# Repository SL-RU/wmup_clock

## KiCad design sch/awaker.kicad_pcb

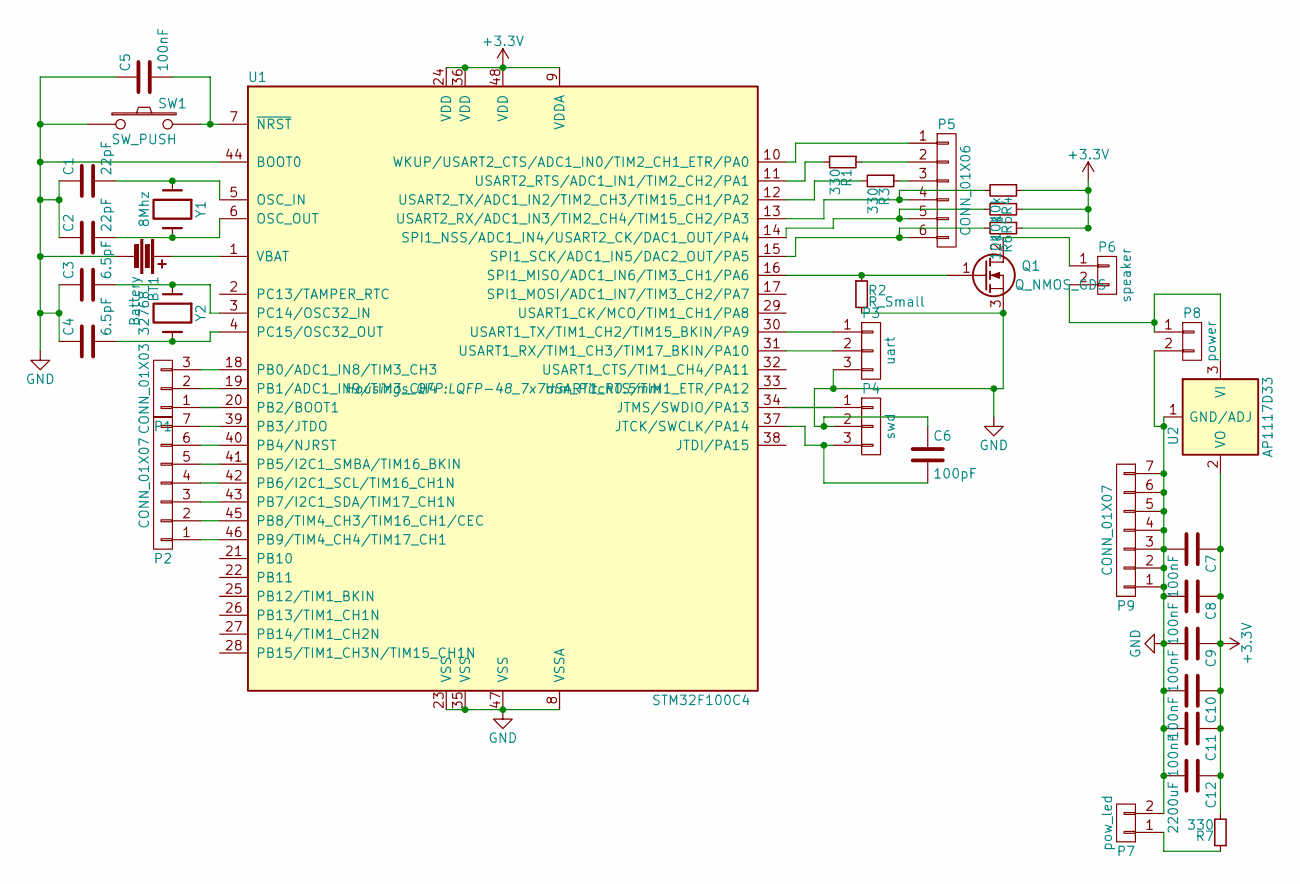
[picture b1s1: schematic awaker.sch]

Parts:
BT1: Battery; BS-7_CR2032
C1, C2: 22pF; C_0402
C3, C4: 6.5pF; C_0805_HandSoldering
C5, C7, C8, C9, C10, C11: 100nF; C_0402
C6: 100pF; C_0805_HandSoldering
C12: 2200uF; C_Radial_D8_L11.5_P3.5
P1: CONN_01X03; Pin_Header_Straight_1x03
P2, P9: CONN_01X07; Pin_Header_Straight_1x07
P3: uart; Pin_Header_Straight_1x03
P4: swd; Pin_Header_Straight_1x03
P5: CONN_01X06; Pin_Header_Straight_1x06
P6: speaker; Pin_Header_Straight_1x02
P7: pow_led; Pin_Header_Straight_1x02
P8: power; Pin_Header_Straight_1x02
Q1: Q_NMOS_GDS; TO-263-3Lead
R1, R3, R7: 330; R_0603
R2: R_Small; R_0603
R4, R5, R6: 10k; R_0603
SW1: SW_PUSH; SW_SPST_EVQQ2
U1: STM32F100C4; LQFP-48_7x7mm_Pitch0.5mm
U2: AP1117D33; SOT-223
Y1: 8Mhz; Crystal_HC49-U_Vertical
Y2: 32768; Crystal_Round_Vertical_3mm

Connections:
+3V3: C7.1, C8.1, C9.1, C10.1, C11.1, C12.1, R4.1, R5.1, R6.1, R7.2, U1.9 (VDDA), U1.24 (VDD), U1.36 (VDD), U1.48 (VDD), U2.2 (VO)
GND: BT1.2, C1.1, C2.1, C3.1, C4.1, C5.1, C6.1, C7.2, C8.2, C9.2, C10.2, C11.2, C12.2, P3.3, P4.2, P7.2, P8.2, P9.1, P9.2, P9.3, P9.4, P9.5, P9.6, P9.7, Q1.3 (S), R2.2, SW1.1, U1.8 (VSSA), U1.23 (VSS), U1.35 (VSS), U1.44 (BOOT0), U1.47 (VSS), U2.1 (GND/ADJ)
unnamed: BT1.1, U1.1 (VBAT)
unnamed: C1.2, U1.5 (OSC_IN), Y1.1
unnamed: C2.2, U1.6 (OSC_OUT), Y1.2
unnamed: C3.2, U1.3 (PC14/OSC32_IN), Y2.1
unnamed: C4.2, U1.4 (PC15/OSC32_OUT), Y2.2
unnamed: C5.2, SW1.2, U1.7 (~NRST)
unnamed: C6.2, P4.3, U1.37 (JTCK/SWCLK/PA14)
unnamed: P1.1, U1.20 (PB2/BOOT1)
unnamed: P1.2, U1.19 (PB1/ADC1_IN9/TIM3_CH4)
unnamed: P1.3, U1.18 (PB0/ADC1_IN8/TIM3_CH3)
unnamed: P2.1, U1.46 (PB9/TIM4_CH4/TIM17_CH1)
unnamed: P2.2, U1.45 (PB8/TIM4_CH3/TIM16_CH1/CEC)
unnamed: P2.3, U1.43 (PB7/I2C1_SDA/TIM17_CH1N)
unnamed: P2.4, U1.42 (PB6/I2C1_SCL/TIM16_CH1N)
unnamed: P2.5, U1.41 (PB5/I2C1_SMBA/TIM16_BKIN)
unnamed: P2.6, U1.40 (PB4/NJRST)
unnamed: P2.7, U1.39 (PB3/JTDO)
unnamed: P3.1, U1.30 (USART1_TX/TIM1_CH2/TIM15_BKIN/PA9)
unnamed: P3.2, U1.31 (USART1_RX/TIM1_CH3/TIM17_BKIN/PA10)
unnamed: P4.1, U1.34 (JTMS/SWDIO/PA13)
unnamed: P5.1, U1.10 (WKUP/USART2_CTS/ADC1_IN0/TIM2_CH1_ETR/P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)
unnamed: P5.2, R1.1
unnamed: P5.3, R3.1
unnamed: P5.4, R4.2, U1.13 (USART2_RX/ADC1_IN3/TIM2_CH4/TIM15_CH2/P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)
unnamed: P5.5, R5.2, U1.14 (SPI1_NSS/ADC1_IN4/USART2_CK/DAC1_OUT/PA4)
unnamed: P5.6, R6.2, U1.15 (SPI1_SCK/ADC1_IN5/DAC2_OUT/PA5)
unnamed: P6.1, Q1.2 (D)
unnamed: P6.2, P8.1, U2.3 (VI)
unnamed: P7.1, R7.1
unnamed: Q1.1 (G), R2.1, U1.16 (SPI1_MISO/ADC1_IN6/TIM3_CH1/PA6)
unnamed: R1.2, U1.11 (USART2_RTS/ADC1_IN1/TIM2_CH2/PA1)
unnamed: R3.2, U1.12 (USART2_TX/ADC1_IN2/TIM2_CH3/TIM15_CH1/P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)

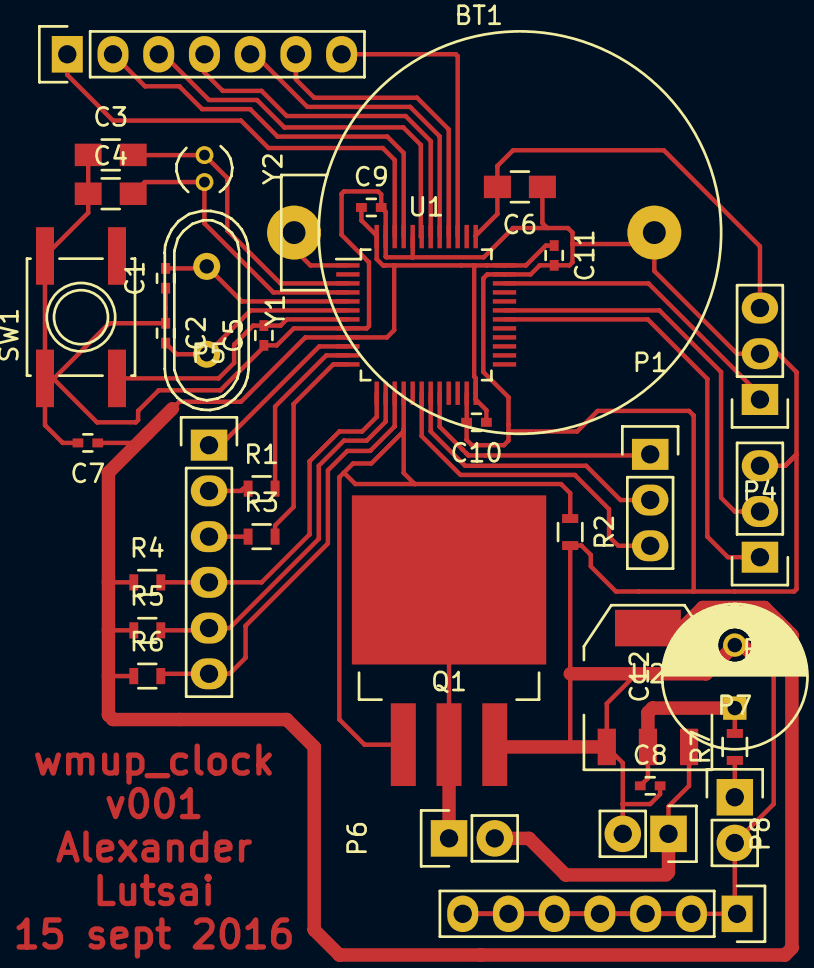
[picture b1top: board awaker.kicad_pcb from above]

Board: 2 copper layers, 35 parts (0 on the bottom side), 34 nets.

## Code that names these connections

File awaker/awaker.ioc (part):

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Mcu.Name=STM32F103C(8-B)Tx
Mcu.Package=LQFP48
Mcu.UserName=STM32F103CBTx
PA10.Mode=Asynchronous
PA10.Signal=USART1_RX
PA13.Mode=Serial_Wire
PA13.Signal=SYS_JTMS-SWDIO
PA14.Mode=Serial_Wire
PA14.Signal=SYS_JTCK-SWCLK
PA7.Signal=GPIO_Output
PA8.Signal=GPIO_Output
PA9.Mode=Asynchronous
PA9.Signal=USART1_TX
PB0.Signal=ADCx_IN8
PB1.Signal=ADCx_IN9
PB11.Signal=GPIO_Output
PB13.Signal=GPIO_Output
PB3.GPIOParameters=GPIO_Label
PB3.GPIO_Label=front_red
PB3.Signal=GPIO_Input
PB4.GPIOParameters=GPIO_Label
PB4.GPIO_Label=front_green
PB4.Signal=GPIO_Input
PB5.GPIOParameters=GPIO_Label
PB5.GPIO_Label=button_BIG
PB5.Signal=GPIO_Input
PB6.Signal=S_TIM4_CH1
PB7.Signal=S_TIM4_CH2
PB8.GPIOParameters=GPIO_Label
PB8.GPIO_Label=button_small
PB8.Signal=GPIO_Input
PC14-OSC32_IN.Mode=LSE-External-Oscillator
PC14-OSC32_IN.Signal=RCC_OSC32_IN
PC15-OSC32_OUT.Mode=LSE-External-Oscillator
PC15-OSC32_OUT.Signal=RCC_OSC32_OUT
PD0-OSC_IN.Mode=HSE-External-Oscillator
PD0-OSC_IN.Signal=RCC_OSC_IN
PD1-OSC_OUT.Mode=HSE-External-Oscillator
PD1-OSC_OUT.Signal=RCC_OSC_OUT
RCC.HSE_VALUE=4000000
RCC.SYSCLKFreq_VALUE=64000000
RCC.SYSCLKSource=RCC_SYSCLKSOURCE_PLLCLK
board=awaker

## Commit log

2016-09-14 first
2016-09-27 reset. New board.
2016-10-04 fix alarm
